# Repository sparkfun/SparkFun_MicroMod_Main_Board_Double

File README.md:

SparkFun MicroMod Main Board - Double
========================================

[*SparkFun MicroMod Main Board - Double (DEV-20595)*](https://www.sparkfun.com/products/20595)

The MicroMod Main Board - Double is a specialized carrier board that allows you to interface a MicroMod Processor Board with up to two MicroMod Function Boards. With the M.2 MicroMod connector, connecting your Processor and Function Boards is a breeze. Simply match up the key on your board's beveled edge connector to the key on the M.2 connector and secure the boards with screws.

The Double Main Board includes one USB-C connector for power and programming the Processor Board. A jumper is available on the back of the board to isolate the USB C's shield pin. Two buttons for reset and boot are also populated on the board. Processor Board pins are also broken out as 2x5 SWD pins. Also, included on the board is a 2A resettable fuse and 3.3V/1A voltage regulator. A second 3.3V/500mA voltage regulator is included on the board to power your Qwiic-enabled devices. We've even added convenient PTH jumpers for advanced users looking to bypass the fuse and measure the current consumption on the 5V and 3.3V lines for low-power testing. For those that need to go remote with their application, the board includes a 2-pin JST connector and a single-cell LiPo MCP73831 charge IC (set to a charge rate of 500mA).

Two switches have been included to toggle between the general-purpose pins and each Function Board's voltage regulator. A third switch has also been included to switch between different SPI chip select pins on the second Function Board. Four status LEDs are available for power and charging. These can also be disabled through the jumpers. There is a microSD card socket so you can also plug in a microSD card for data logging. The microSD socket can be disabled through the I/O pins. Finally, two Qwiic connectors are populated on the board with built-in pull-up resistors to easily add Qwiic-enabled I<sup>2</sup>C devices to your projects!

Repository Contents
-------------------

* **/Firmware** - Arduino example code from the tutorial
* **/Hardware** - Eagle design files (.brd, .sch)
* **/Production** - Production panel files (.brd)

Documentation
--------------

* **[Hookup Guide V2](https://learn.sparkfun.com/tutorials/2683)** - Basic hookup guide

Product Versions
----------------
* [DEV-20595](https://www.sparkfun.com/products/20595)- Initial release, v2.2
* [DEV-18576](https://www.sparkfun.com/products/18576)- Initial release, v1.1

Version History
---------------
* v2.2
* v1.1 - Initial Release

License Information
-------------------

This product is _**open source**_! 

Please review the LICENSE.md file for license information. 

If you have any questions or concerns on licensing, please contact technical support on our [SparkFun forums](https://forum.sparkfun.com/viewforum.php?f=152).

Distributed as-is; no warranty is given.

- Your friends at SparkFun.

_<COLLABORATION CREDIT>_

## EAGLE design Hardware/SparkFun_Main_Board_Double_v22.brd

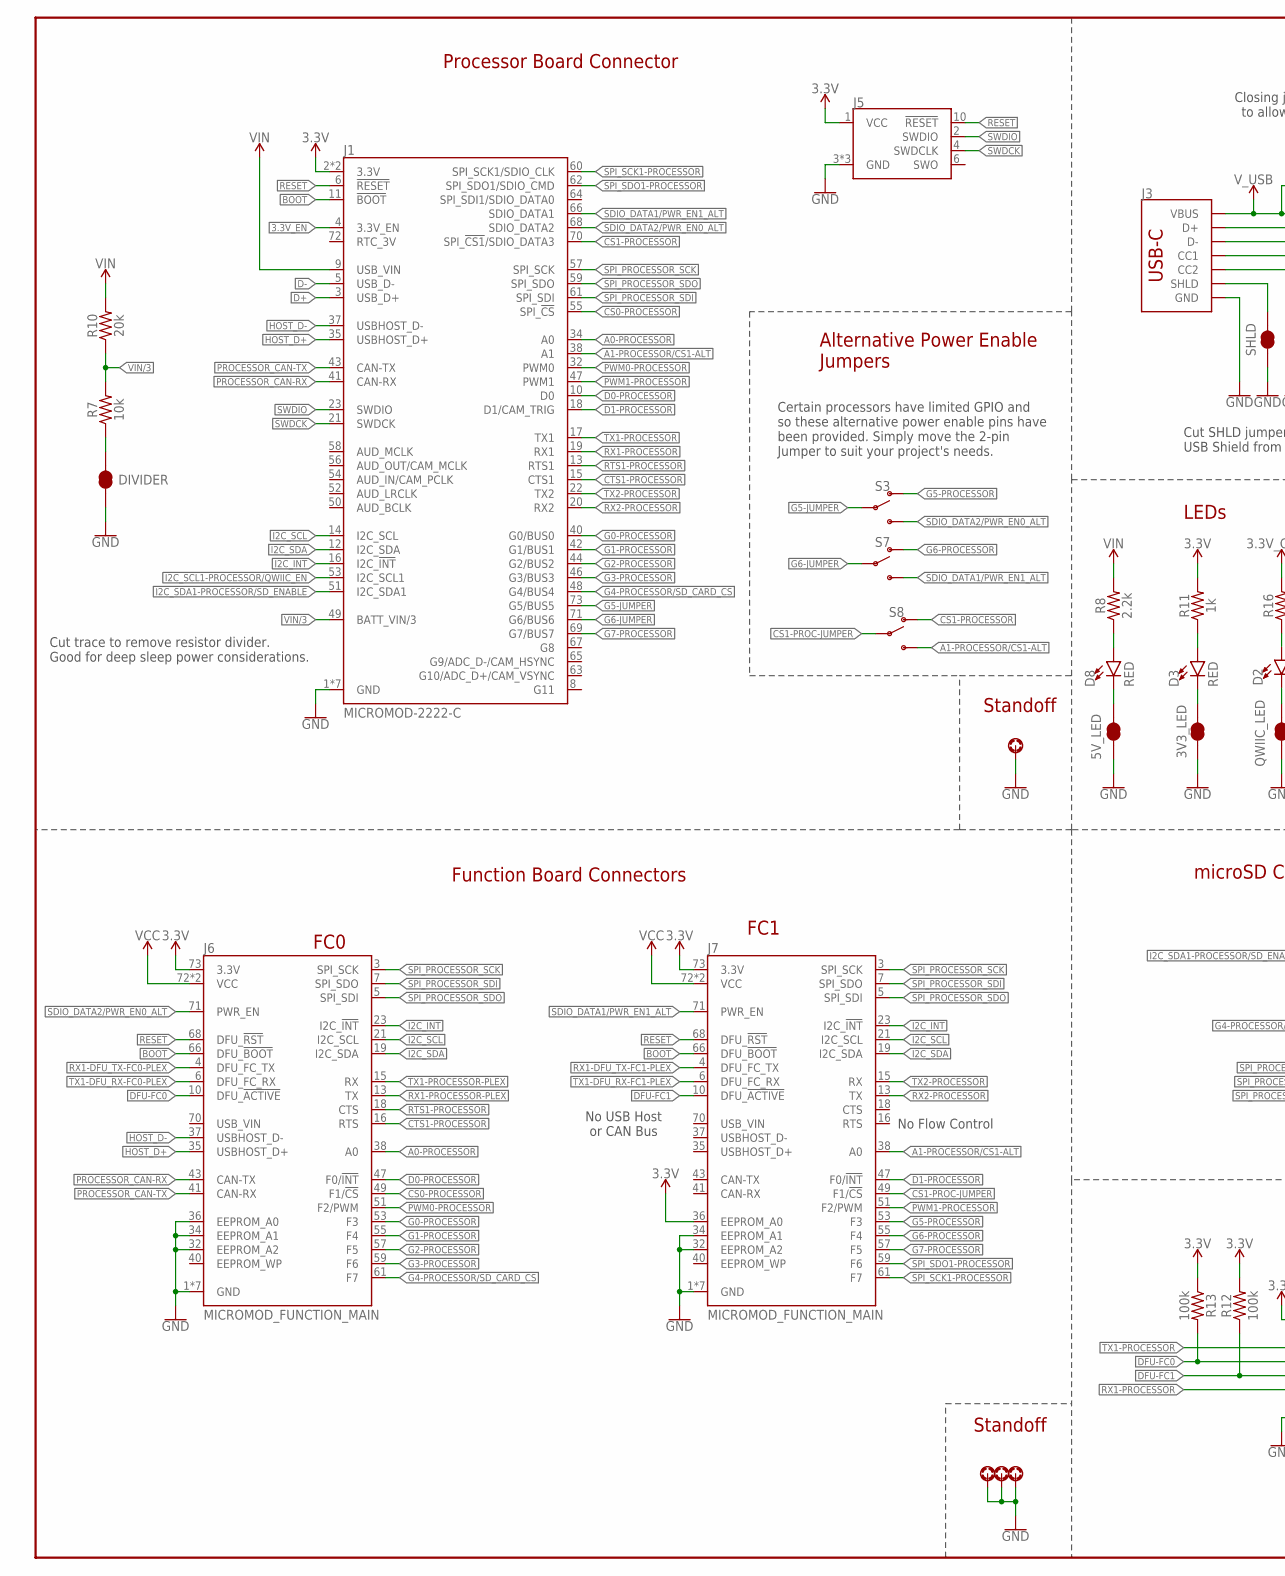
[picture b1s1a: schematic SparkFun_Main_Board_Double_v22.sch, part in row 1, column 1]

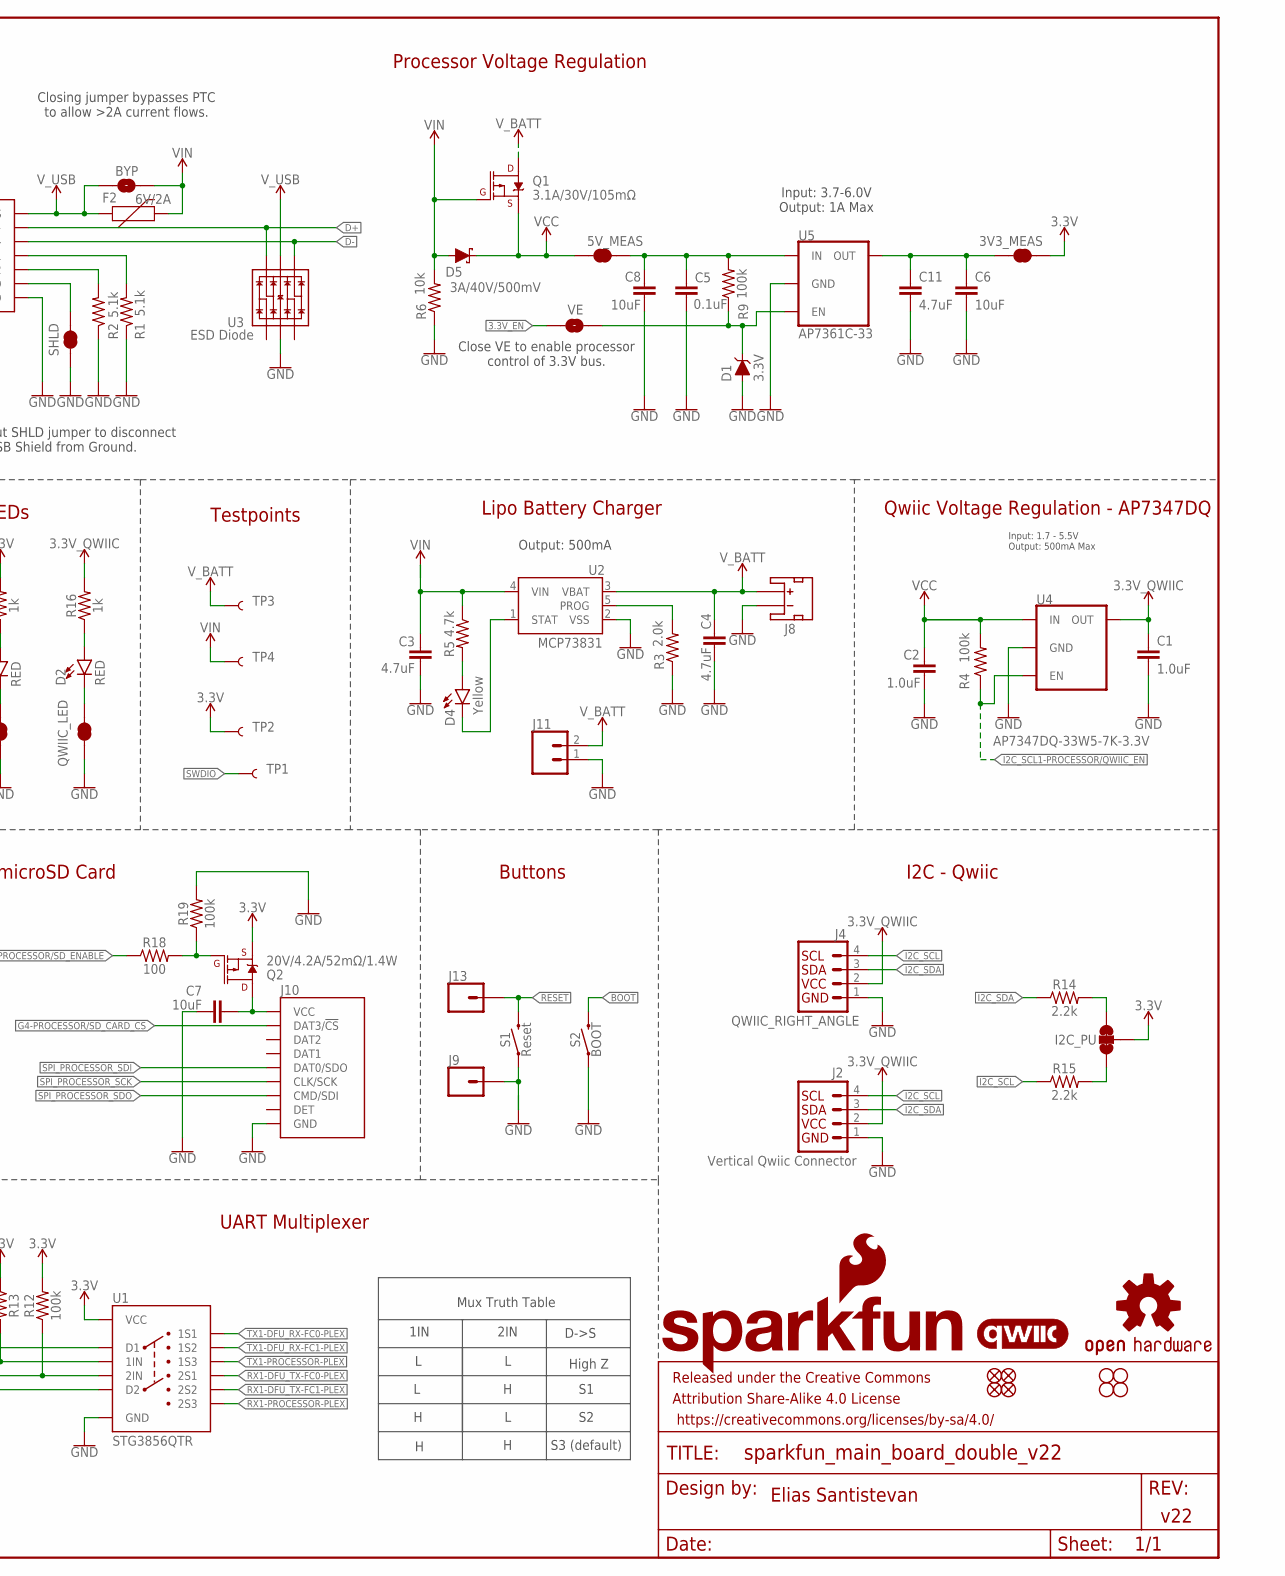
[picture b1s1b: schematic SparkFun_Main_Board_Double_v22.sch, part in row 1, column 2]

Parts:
3V3_LED, 5V_LED: JUMPER-SMT_2_NC_TRACE_SILK; SMT-JUMPER_2_NC_TRACE_SILK
3V3_MEAS, 5V_MEAS: JUMPER-COMBO_2_NC_TRACE; COMBO-JUMPER_2_NC_TRACE
BYP: JUMPER-SMT_2_NO_SILK; SMT-JUMPER_2_NO_SILK
C1, C2: 1.0uF; 0603
C3, C4, C11: 4.7uF; 0603
C5: 0.1uF; 0603
C6, C8: 10uF; 0805
C7: 10uF; 0603
D1: 3.3V; SOD-323
D2, D3, D8: RED; LED-0603
D4: Yellow; LED-0603
D5: 3A/40V/500mV; SMA-DIODE
DIVIDER: JUMPER-SMT_2_NC_TRACE_SILK; SMT-JUMPER_2_NC_TRACE_SILK
F2: 6V/2A; 1210
FD1, FD2, FD3, FD4: FIDUCIAL1X2; FIDUCIAL-1X2
FRAME1: FRAME-LEDGER; CREATIVE_COMMONS
H2, H3, H4, H8: STAND-OFF-REFLOW-M2.5_2.5MM_TALL; STAND-OFF-REFLOW-M2.5
H14, H15, H16, H17: STAND-OFFTIGHT; STAND-OFF-TIGHT
I2C_PU: JUMPER-SMT_3_2-NC_TRACE_SILK; SMT-JUMPER_3_2-NC_TRACE_SILK
J1: MICROMOD-2222-C; M.2-CONNECTOR-E
J2: Vertical Qwiic Connector; JST04_1MM_VERT
J3: USB_C_2-LAYER_PADS; USB-C-16P-2LAYER-PADS
J4: QWIIC_RIGHT_ANGLE; JST04_1MM_RA
J5: CORTEX_JTAG_DEBUG_MINIMUM_PTH; 2X5-PTH-1.27MM
J6, J7: MICROMOD_FUNCTION_MAIN; M.2-CONNECTOR-E-FUNCTION-STANDARD
J8: JST_2MM_MALE; JST-2-SMD
J9, J13: CONN_01PTH_NO_SILK_YES_STOP; 1X01_NO_SILK
J10: MICRO-SD-PUSH-PUSH-EXT-PIN; MICROSD-EXTERNALPIN
J11: CONN_021X02_NO_SILK; 1X02_NO_SILK
LOGO1: QWIIC_LOGO_8MM; QWIIC_8MM
LOGO2: SFE_LOGO_NAME_FLAME.3_INCH; SFE_LOGO_NAME_FLAME_.3
LOGO3: OSHW-LOGOL; OSHW-LOGO-L
Q1: 3.1A/30V/105mΩ; SOT23-3
Q2: 20V/4.2A/52mΩ/1.4W; SOT23-3
QWIIC_LED: JUMPER-SMT_2_NC_TRACE_SILK; SMT-JUMPER_2_NC_TRACE_SILK
R1, R2: 5.1k; 0603
R3: 2.0k; 0603
R4, R9, R12, R13, R19: 100k; 0603
R5: 4.7k; 0603
R6, R7: 10k; 0603
R8, R14, R15: 2.2k; 0603
R10: 20k; 0603
R11, R16: 1k; 0603
R18: 100; 0603
S1: Reset; TACTILE_SWITCH_SMD_5.2MM
S2: BOOT; TACTILE_SWITCH_SMD_5.2MM
S3, S7, S8: SWITCH-SPDT-SMD-RIGHT-ANGLE; SWITCH_SPST_SMD_A
SHLD: JUMPER-SMT_2_NC_TRACE_SILK; SMT-JUMPER_2_NC_TRACE_SILK
TP1, TP2, TP3, TP4: TEST-POINT3X5; PAD.03X.05
U1: STG3856QTR; STG3856
U2: MCP73831; SOT23-5
U3: ESD Diode; SOT-23-6
U4: AP7347DQ-33W5-7K-3.3V; SOT25
U5: AP7361C-33; UDFN-8
VE: JUMPER-SMT_2_NO_SILK; SMT-JUMPER_2_NO_SILK

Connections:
3.3V: 3V3_MEAS.2, 3V3_MEAS.4 (2), I2C_PU.2, J1.2 (3.3V), J1.74 (3.3V), J5.1 (VCC), J6.73 (3.3V), J7.36 (EEPROM_A0), J7.73 (3.3V), Q2.2 (S), R11.2, R12.2, R13.1, TP2.1, U1.P11 (VCC)
3.3V_EN: J1.4 (3.3V_EN), VE.1
3.3V_EN_VE: D1.C, R9.1, U5.5 (EN), VE.2
3.3V_QWIIC: C1.1, J2.2, J4.2, R16.2, U4.5 (OUT)
3V3_MEAS: 3V3_MEAS.1, 3V3_MEAS.3 (1), C6.1, C11.1, U5.1 (OUT)
5V_MEAS: 5V_MEAS.2, 5V_MEAS.4 (2), C5.1, C8.1, R9.2, U5.8 (IN)
!BOOT!: J1.11 (!BOOT!), J6.66 (DFU_!BOOT!), J7.66 (DFU_!BOOT!), S2.3 (2), S2.4 (2)
!CS0!-PROCESSOR: J1.55 (SPI_!CS!), J6.49 (F1/!CS!)
!CS1!-PROC-JUMPER: J7.49 (F1/!CS!), S8.2
!CS1!-PROCESSOR: J1.70 (SPI_!CS1!/SDIO_DATA3), S8.1 (O)
!DFU-FC0!: J6.10 (DFU_!ACTIVE!), R13.2, U1.P12 (1IN)
!DFU-FC1!: J7.10 (DFU_!ACTIVE!), R12.1, U1.P10 (2IN)
!RESET!: J1.6 (!RESET!), J5.10 (!RESET), J6.68 (DFU_!RST!), J7.68 (DFU_!RST!), J13.1, S1.3 (2), S1.4 (2)
A0-PROCESSOR: J1.34 (A0), J6.38 (A0)
A1-PROCESSOR/!CS1!-ALT: J1.38 (A1), J7.38 (A0), S8.3 (S)
CTS1-PROCESSOR: J1.15 (CTS1), J6.16 (RTS)
D0-PROCESSOR: J1.10 (D0), J6.47 (F0/!INT!)
D1-PROCESSOR: J1.18 (D1/CAM_TRIG), J7.47 (F0/!INT!)
D+: J1.3 (USB_D+), J3.A6 (D+), J3.B6 (D+), U3.6 (IO4)
D-: J1.5 (USB_D-), J3.A7 (D-), J3.B7 (D-), U3.4 (IO3)
G0-PROCESSOR: J1.40 (G0/BUS0), J6.53 (F3)
G1-PROCESSOR: J1.42 (G1/BUS1), J6.55 (F4)
G2-PROCESSOR: J1.44 (G2/BUS2), J6.57 (F5)
G3-PROCESSOR: J1.46 (G3/BUS3), J6.59 (F6)
G4-PROCESSOR/SD_CARD_!CS!: J1.48 (G4/BUS4), J6.61 (F7), J10.2 (DAT3/!CS!)
G5-JUMPER: J1.73 (G5/BUS5), S3.2
G5-PROCESSOR: J7.53 (F3), S3.1 (O)
G6-JUMPER: J1.71 (G6/BUS6), S7.2
G6-PROCESSOR: J7.55 (F4), S7.1 (O)
G7-PROCESSOR: J1.69 (G7/BUS7), J7.57 (F5)
GND: 3V3_LED.1, 5V_LED.1, C1.2, C2.2, C3.2, C4.2, C5.2, C6.2, C7.1, C8.2, C11.2, D1.A, DIVIDER.1, H2.1, H3.1, H4.1, H8.1, J1.1 (GND), J1.7 (GND), J1.33 (GND), J1.36 (GND), J1.39 (GND), J1.45 (GND), J1.75 (GND), J2.1, J3.GND, J3.GND2 (GND), J4.1, J5.3 (GND), J5.5 (GND), J5.9 (GND), J6.1 (GND), J6.2 (GND), J6.8 (GND), J6.32 (EEPROM_A2), J6.33 (GND), J6.34 (EEPROM_A1), J6.36 (EEPROM_A0), J6.39 (GND), J6.45 (GND), J6.75 (GND), J7.1 (GND), J7.2 (GND), J7.8 (GND), J7.32 (EEPROM_A2), J7.33 (GND), J7.34 (EEPROM_A1), J7.39 (GND), J7.45 (GND), J7.75 (GND), J8.1 (-), J9.1, J10.6 (GND), J10.10 (GND), J10.11 (GND), J10.12 (GND), J10.13 (GND), J11.1, QWIIC_LED.1, R1.1, R2.1, R3.1, R6.1, R19.2, S1.1, S1.2 (1), S2.1, S2.2 (1), SHLD.1, U1.P5 (GND), U2.2 (VSS), U3.2 (VSS), U4.2 (GND), U5.4 (GND), U5.EP (GND)
HOST_D+: J1.35 (USBHOST_D+), J6.35 (USBHOST_D+)
HOST_D-: J1.37 (USBHOST_D-), J6.37 (USBHOST_D-)
I2C_!INT!: J1.16 (I2C_!INT!), J6.23 (I2C_!INT!), J7.23 (I2C_!INT!)
I2C_SCL: J1.14 (I2C_SCL), J2.4, J4.4, J6.21 (I2C_SCL), J7.21 (I2C_SCL), R15.1
I2C_SCL1-PROCESSOR/QWIIC_EN: J1.53 (I2C_SCL1), R4.1, U4.3 (EN)
I2C_SDA: J1.12 (I2C_SDA), J2.3, J4.3, J6.19 (I2C_SDA), J7.19 (I2C_SDA), R14.1
I2C_SDA1-PROCESSOR/!SD_ENABLE!: J1.51 (I2C_SDA1), R18.1
unnamed: D4.A, R5.2
unnamed: 5V_LED.2, D8.C
unnamed: D3.A, R11.1
unnamed: J3.B5 (CC2), R2.2
unnamed: J3.A5 (CC1), R1.2
unnamed: R3.2, U2.5 (PROG)
unnamed: DIVIDER.2, R7.1
unnamed: D2.C, QWIIC_LED.2
unnamed: D2.A, R16.1
unnamed: 3V3_LED.2, D3.C
unnamed: I2C_PU.3, R14.2
unnamed: D8.A, R8.1
unnamed: I2C_PU.1, R15.2
unnamed: D4.C, U2.1 (STAT)
unnamed: C7.2, J10.4 (VCC), Q2.3 (D)
unnamed: Q2.1 (G), R18.2, R19.1
PROCESSOR_CAN-RX: J1.41 (CAN-RX), J6.43 (CAN-TX)
PROCESSOR_CAN-TX: J1.43 (CAN-TX), J6.41 (CAN-RX)
PWM0-PROCESSOR: J1.32 (PWM0), J6.51 (F2/PWM)
PWM1-PROCESSOR: J1.47 (PWM1), J7.51 (F2/PWM)
RTS1-PROCESSOR: J1.13 (RTS1), J6.18 (CTS)
RX1-DFU_TX-FC0-PLEX: J6.4 (DFU_FC_TX), U1.P9 (2S1)
RX1-DFU_TX-FC1-PLEX: J7.4 (DFU_FC_TX), U1.P8 (2S2)
RX1-PROCESSOR: J1.19 (RX1), U1.P6 (D2)
RX1-PROCESSOR-PLEX: J6.13 (TX), U1.P7 (2S3)
RX2-PROCESSOR: J1.20 (RX2), J7.13 (TX)
SDIO_DATA1/PWR_EN1_ALT: J1.66 (SDIO_DATA1), J7.71 (PWR_EN), S7.3 (S)
SDIO_DATA2/PWR_EN0_ALT: J1.68 (SDIO_DATA2), J6.71 (PWR_EN), S3.3 (S)
SHLD: J3.SHLD1 (SHLD), J3.SHLD2 (SHLD), J3.SHLD3 (SHLD), J3.SHLD4 (SHLD), SHLD.2
SPI_PROCESSOR_SCK: J1.57 (SPI_SCK), J6.3 (SPI_SCK), J7.3 (SPI_SCK), J10.5 (CLK/SCK)
SPI_PROCESSOR_SDI: J1.61 (SPI_SDI), J6.7 (SPI_SDO), J7.7 (SPI_SDO), J10.7 (DAT0/SDO)
SPI_PROCESSOR_SDO: J1.59 (SPI_SDO), J6.5 (SPI_SDI), J7.5 (SPI_SDI), J10.3 (CMD/SDI)
SPI_SCK1-PROCESSOR: J1.60 (SPI_SCK1/SDIO_CLK), J7.61 (F7)
SPI_SDO1-PROCESSOR: J1.62 (SPI_SDO1/SDIO_CMD), J7.59 (F6)
SWDCK: J1.21 (SWDCK), J5.4 (SWDCLK)
SWDIO: J1.23 (SWDIO), J5.2 (SWDIO), TP1.1
TX1-DFU_RX-FC0-PLEX: J6.6 (DFU_FC_RX), U1.P1 (1S1)
TX1-DFU_RX-FC1-PLEX: J7.6 (DFU_FC_RX), U1.P2 (1S2)
TX1-PROCESSOR: J1.17 (TX1), U1.P4 (D1)
TX1-PROCESSOR-PLEX: J6.15 (RX), U1.P3 (1S3)
TX2-PROCESSOR: J1.22 (TX2), J7.15 (RX)
VCC: 5V_MEAS.1, 5V_MEAS.3 (1), C2.1, D5.C, J6.72 (VCC), J6.74 (VCC), J7.72 (VCC), J7.74 (VCC), Q1.2 (S), R4.2, U4.1 (IN)
VIN: BYP.2, C3.1, D5.A, F2.2, J1.9 (USB_VIN), Q1.1 (G), R5.1, R6.2, R8.2, R10.2, TP4.1, U2.4 (VIN)
VIN/3: J1.49 (BATT_VIN/3), R7.2, R10.1
V_BATT: C4.1, J8.2 (+), J11.2, Q1.3 (D), TP3.1, U2.3 (VBAT)
V_USB: BYP.1, F2.1, J3.VBUS1 (VBUS), J3.VBUS2 (VBUS), U3.5 (VCC)

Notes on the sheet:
Function Board Connectors
Processor Board Connector
v22
microSD Card
I2C - Qwiic
FC0
FC1
No USB Host or CAN Bus
No Flow Control
Lipo Battery Charger
Testpoints
Processor Voltage Regulation
Closing jumper bypasses PTC to allow >2A current flows.
Input: 3.7-6.0V Output: 1A Max
Close VE to enable processor control of 3.3V bus.
LEDs
Buttons
Elias Santistevan
Standoff
Alternative Power Enable Jumpers
Certain processors have limited GPIO and so these alternative power enable pins have been provided. Simply move the 2-pin Jumper to suit your project's needs.
Mux Truth Table
1IN
2IN
D->S
High Z
S3 (default)
UART Multiplexer
Qwiic Voltage Regulation - AP7347DQ
Input: 1.7 - 5.5V Output: 500mA Max
Output: 500mA
Cut SHLD jumper to disconnect USB Shield from Ground.
Cut trace to remove resistor divider. Good for deep sleep power considerations.

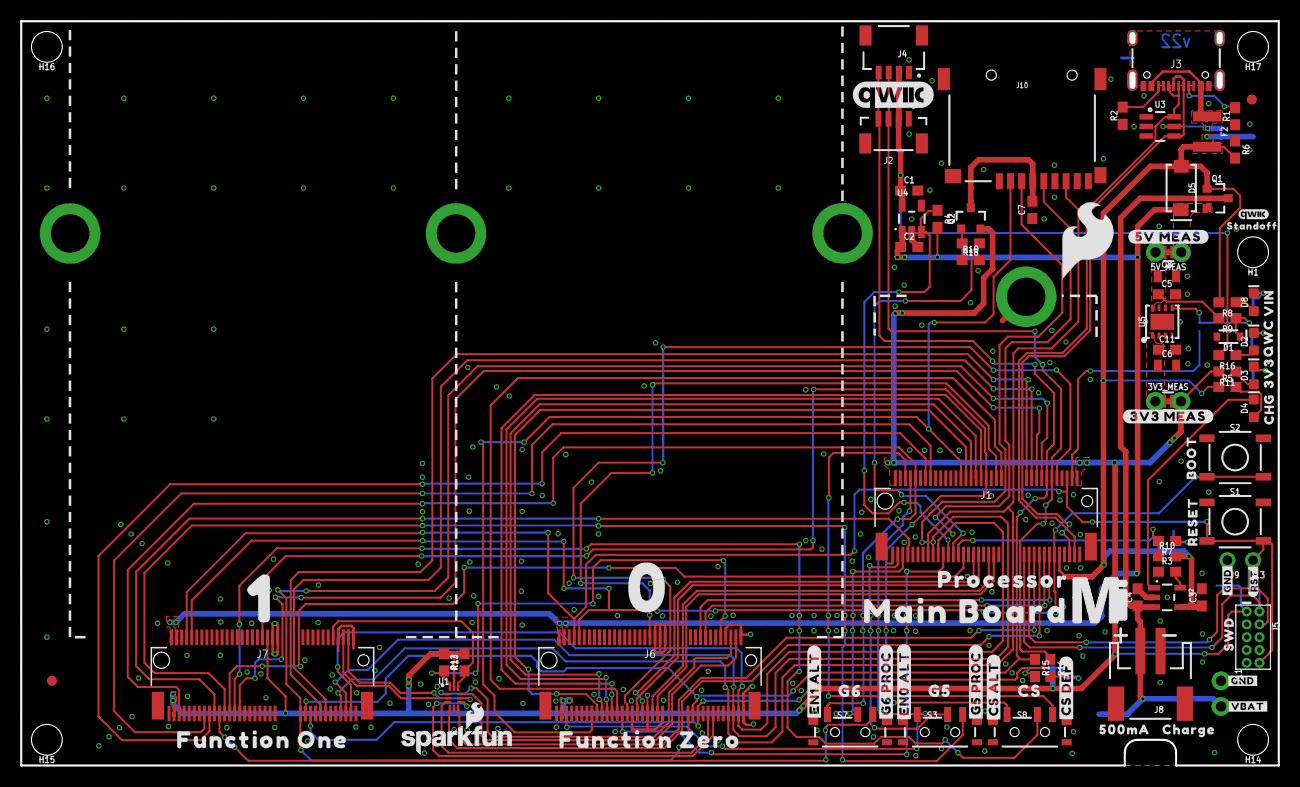
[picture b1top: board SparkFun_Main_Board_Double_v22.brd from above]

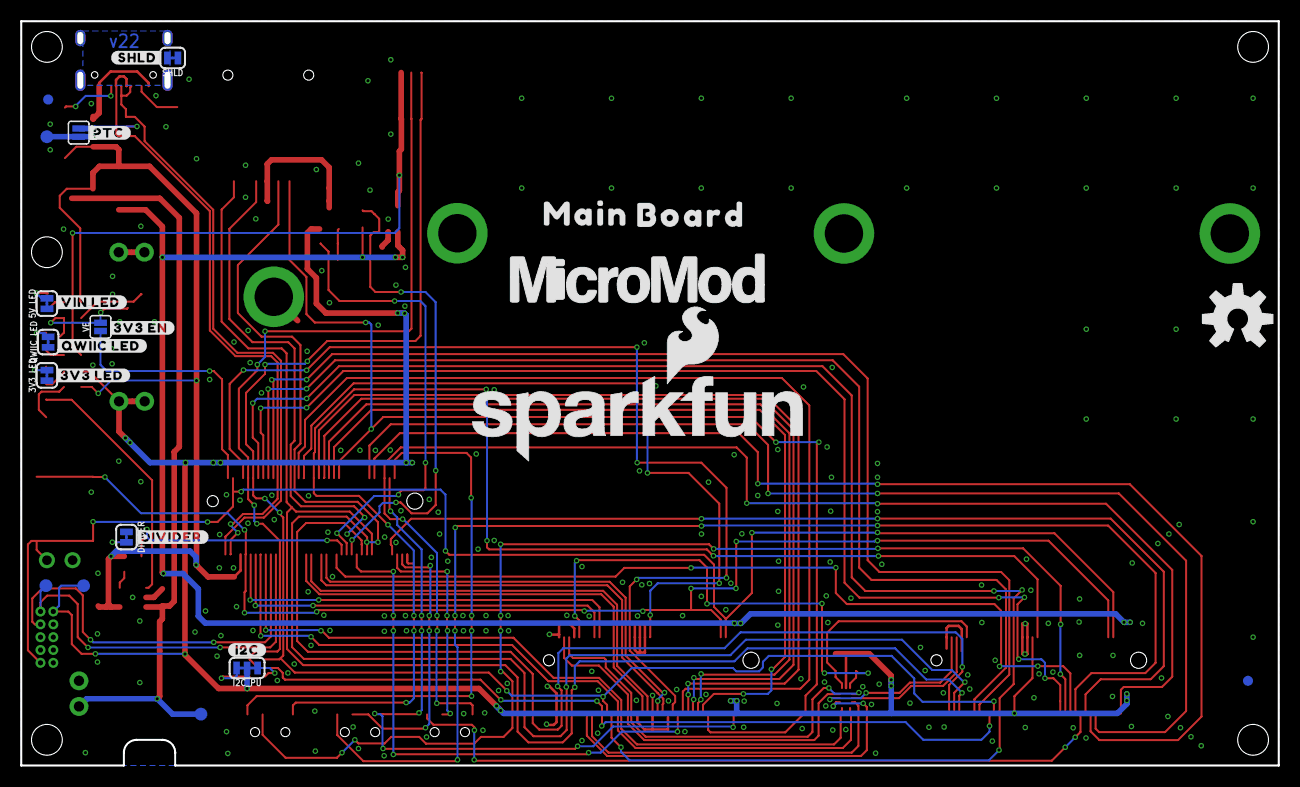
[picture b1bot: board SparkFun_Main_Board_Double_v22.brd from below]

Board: 2 copper layers, 124.5 x 73.7 mm, 136 parts (27 on the bottom side), 84 nets.

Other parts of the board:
FRAME2: FRAME-LEDGERNO_FOOTPRINT; DUMMY
H1: STAND-OFFTIGHT; STAND-OFF-TIGHT
U$1: #3V3_LED#22
U$2: #3V3_EN#23
U$3: ##RST##8
U$4: 3V332533
U$5: VIN32532
U$6: CHG32531
U$7: #SHLD#501
U$8: BOOT32541
U$9: RESET32540
U$10: PROCESSOR525
U$11: FUNCTION_ZERO520
U$12: FUNCTION_ONE524
U$13: MAIN523
U$14: MICROMOD_MI_LOGO_1
U$15: 0523
U$16: 1524
U$17: MICROMOD_LOGO_1
U$18: BOARD524
U$19: G518
U$20: #CS_ALT#20
U$21: MAIN_BOARD5523
U$22: QWIIC_3MM
U$23: STANDOFF501
U$24: SFE_LOGO_FLAME_.3
U$25: SWD6522
U$26: #3V3_MEAS#6522
U$27: CHARGE501
U$28: #QWIIC_LED#22
U$29: G6519
U$30: #I2C#501
U$31: #5V_MEAS#6522
U$32: CS17
U$33: 500MA6520
U$34: #CS_DEF#19
U$35: #G5_PROC#21
U$36: #G6_PROC#21
U$37: #EN0_ALT#21
U$38: #EN1_ALT#21
U$39, U$40: #GND#10
U$41: #DIVIDER#23
U$42: #VIN_LED#24
U$43: QWC18
U$44: SFE_LOGO_NAME_FLAME_.1
U$45: #PTC#13
U$46: #VBAT#9

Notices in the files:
parts and their libraries:
SparkFun-Connectors: Licensing: Creative Commons ShareAlike 4.0 International - https://creativecommons.org/licenses/by-sa/4.0
SparkFun-Aesthetics: Released under the Creative Commons Attribution Share-Alike 4.0 License
SparkFun-Aesthetics: https://creativecommons.org/licenses/by-sa/4.0
